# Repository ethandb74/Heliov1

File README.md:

# Heliov1
Hand tracking Solar panel module
IDEA/Concept: Robotic Appendage that is idle and tracks sun to get powered. Then there is a Manual Override mode which is controlled by Hand Motions (Inspired by Tony Stark) The inspiration is robotic arms that build and maintain space systems like the CANADARM of the ISS. Because I have a big passion for Space. What I am actually building is a prototype or model of that. I will make a Cad container that will contain two metal servos that Pan and Tilt. at the end their is a solar panel attached. I have a python script (python --> pyfirmata + MP+pysolar ---> arduino) that 1. tracks the location of the sun and points the appendage at it.and 2. has mode switching capabilities to manual ovveride. There is no robotic Gripper as this is v1 proof of concept. 

Below is a preview of the project. 

Below is the full cad with the electroninc componants inserted insde. 

My electroinc wiring. It is very simple the only issue was getting the right power for the metal servos. They cant be powerd directly from the arduino as the draw too much current. To workaround this I use and external power supply; I used an AC to DC adapter and step down to 5v 5a which is perfect for the servos. (notice the common ground but nothing powerd from ardunio):

For the CAD design I did use multiple sorces as reference but the actual desing was made from scratch. Fusion 360:

**Firmware**
I used a variety of libraries- OpenCV and MP for the hand tracking. Very simple to work with. For suntracking I used pysolar.

Handtracking.

PCB:
This project is for a Competition and they required the creation of a PCB for this project. In order to create a PCB that actually solved an existing problem (instead of fabricating a problem to make a pcb around) I  decided to replace my previous Power Distribution system which was a poorly soldered perfboard that connected to my external pwoer suppply. 
See Below: 

To improve this I designed a super simple PCB that uses pin sockets that I instead plug wires into:

-
Bill of Materials

Componant: Arduino,
Servo MG 9996R,
Jumper Wires,
Stranded core copper wire,
Perfboard

Quantity: 1x, 2x, 6x, 5x, 1x

see full [BOM.md](./BOM.md)

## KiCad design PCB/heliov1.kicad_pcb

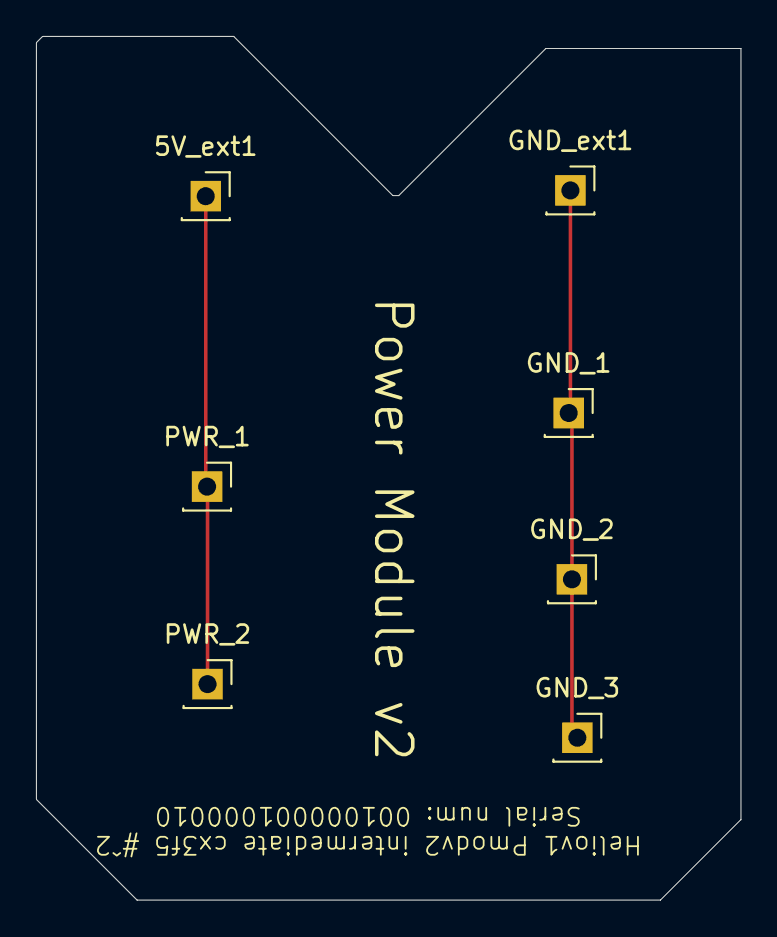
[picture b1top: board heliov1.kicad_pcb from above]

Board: 2 copper layers, 39.1 x 48.0 mm, 7 parts (0 on the bottom side), 2 nets.

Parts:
5V_ext1: Conn_01x01_Socket; PinSocket_1x01_P2.54mm_Vertical
GND_1, GND_2, GND_3: Conn_01x01_Socket; PinSocket_1x01_P2.54mm_Vertical
GND_ext1: Conn_01x01_Socket; PinSocket_1x01_P2.54mm_Vertical
PWR_1, PWR_2: Conn_01x01_Socket; PinSocket_1x01_P2.54mm_Vertical

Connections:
unnamed: 5V_ext1.1, PWR_1.1, PWR_2.1
unnamed: GND_1.1, GND_2.1, GND_3.1, GND_ext1.1

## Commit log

2026-04-08 Rename Enclosure.step to CAD/Enclosure.step
2026-04-08 Rename Internal1.step to CAD/Internal1.step
2026-04-08 Rename PEG.step to CAD/PEG.step
2026-04-08 Rename TopHing1.step to CAD/TopHing1.step
2026-04-08 Rename TopShelf.step to CAD/TopShelf.step
2026-04-08 Rename Heliov1.py to firmware/Heliov1.py
2026-04-28 Rename Enclosure.stl to Production/Enclosure.stl
2026-04-28 Rename Internal1.stl to Production/Internal1.stl
2026-04-28 Rename TopHing1.stl to Production/TopHing1.stl
2026-04-28 Rename TopShelf.stl to Production/TopShelf.stl
2026-04-28 Rename PEG.stl to Production/PEG.stl
2026-04-28 Source files
    I added the cad sorce file
2026-04-28 Rename PanTiltHelio-v3_.f3z to CAD/PanTiltHelio-v3_.f3z
2026-04-29 Update README.md
    fix readme
2026-04-29 sorce file
2026-04-29 Rename PanTiltHeliov3.step to CAD/.PanTiltHeliov3.step
2026-06-05 Rename heliov1-B_Cu.gbr to Production/heliov1-B_Cu.gbr
2026-06-05 Rename heliov1-B_Mask.gbr to Production/heliov1-B_Mask.gbr
2026-06-05 Rename heliov1-B_Paste.gbr to Production/heliov1-B_Paste.gbr
2026-06-05 Rename heliov1-B_Silkscreen.gbr to Production/Heliov1-B_Silkscreen.gbr
2026-06-05 Rename heliov1-Edge_Cuts.gbr to Production/heliov1-Edge_Cuts.gbr
2026-06-05 Rename heliov1-job.gbrjob to Produciton/heliov1-job.gbrjob
2026-06-05 Rename heliov1-PTH.drl to Production/heliov1-PTH.drl
2026-06-05 Rename heliov1-NPTH.drl to Production/heliov1-NPTH.drl
2026-06-05 Rename heliov1-F_Silkscreen.gbr to Production/heliov1-F_Silkscreen.gbr
2026-06-05 Rename heliov1-F_Paste.gbr to Production/heliov1-F_Paste.gbr
2026-06-05 Rename heliov1-F_Mask.gbr to Production/heliov1-F_Mask.gbr
2026-06-05 Rename heliov1-F_Cu.gbr to Production/heliov1-F_Cu.gbr
2026-06-05 Rename heliov1.kicad_pcb to PCB/heliov1.kicad_pcb
2026-06-05 Rename heliov1.kicad_pro to PCB/heliov1.kicad_pro
